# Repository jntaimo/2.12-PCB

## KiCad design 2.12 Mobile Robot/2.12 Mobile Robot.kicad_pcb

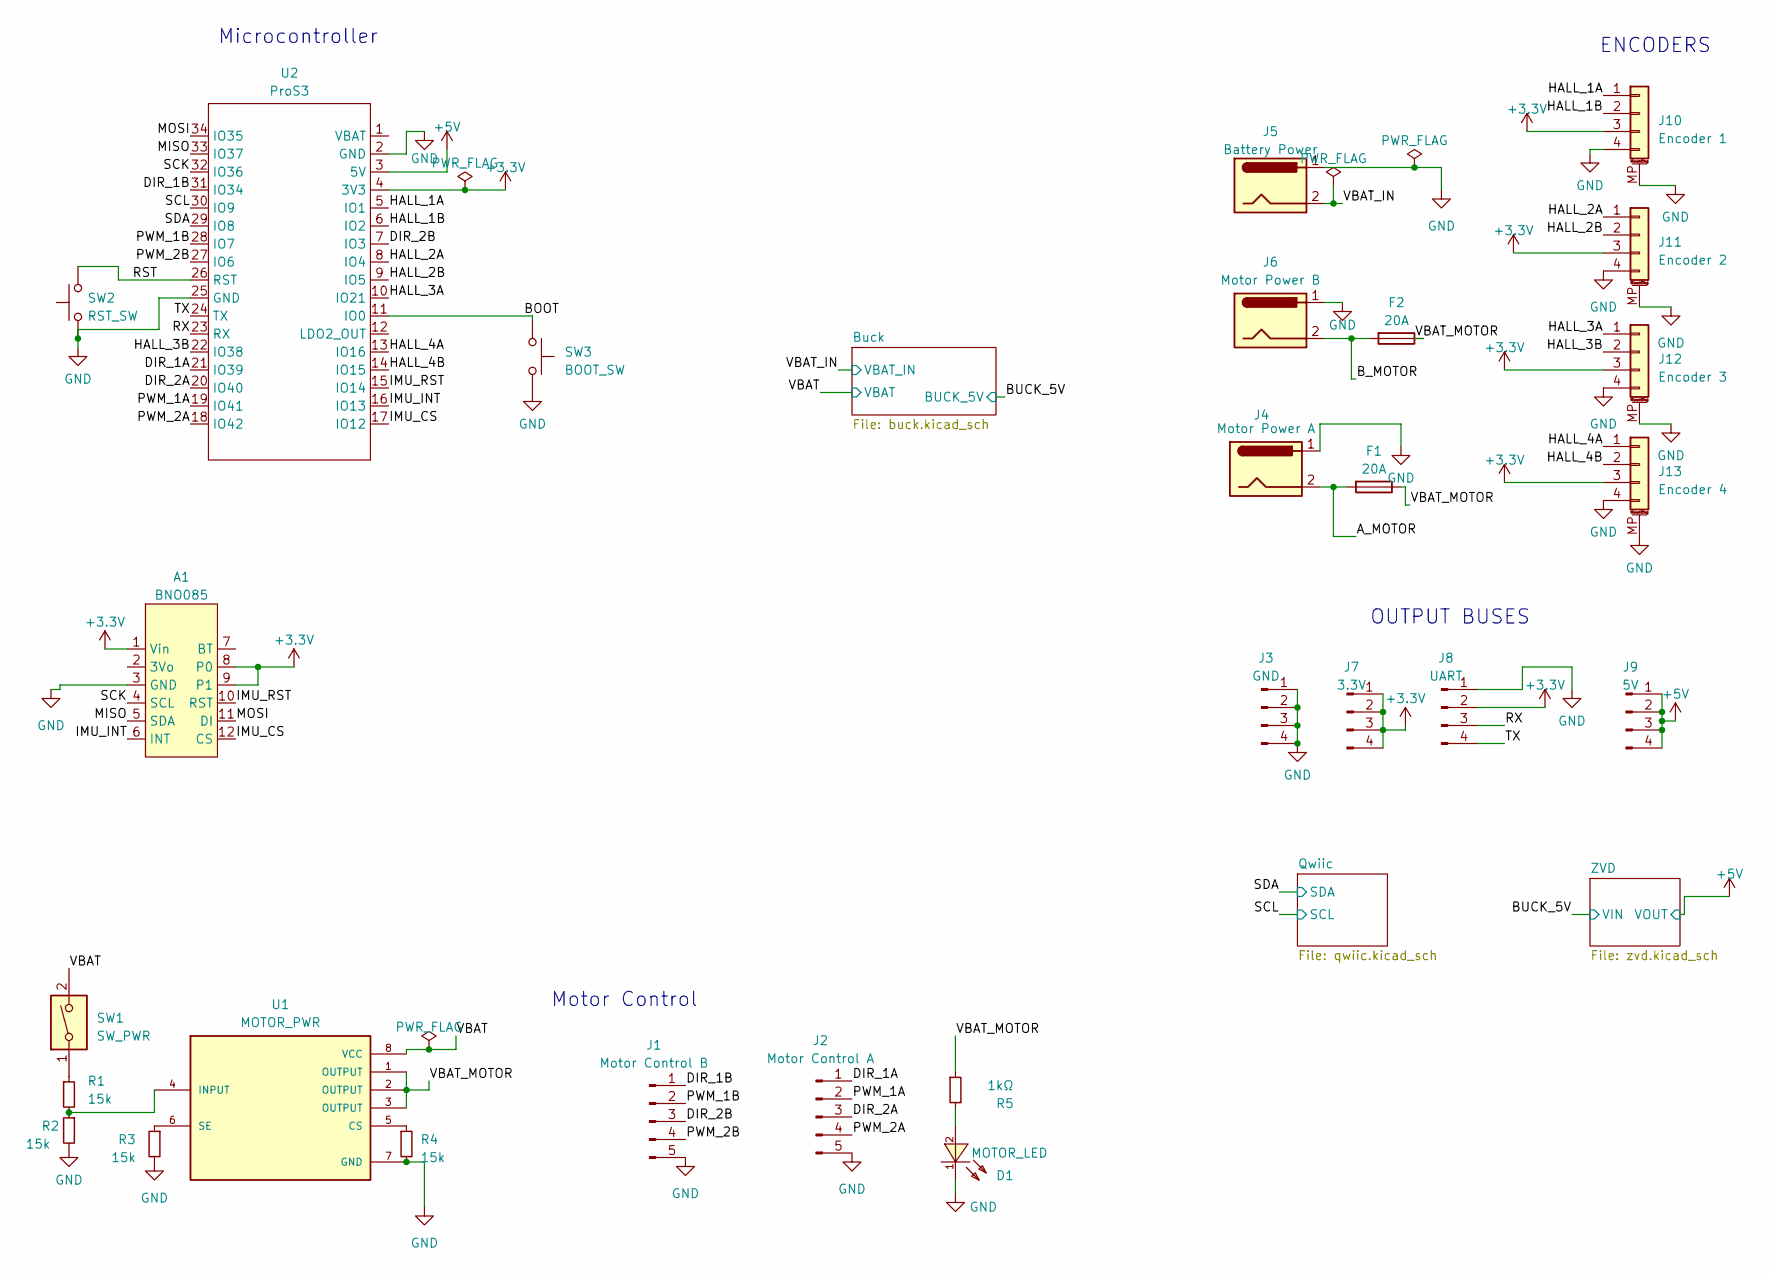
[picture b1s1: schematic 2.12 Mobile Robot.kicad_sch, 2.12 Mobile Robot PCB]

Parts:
A1: BNO085; Adafruit_BNO085
D1: MOTOR_LED; LED0603; LCSC C2286
F1, F2: 20A; Fuse_1206_3216Metric; MPN C207007
J1: Motor Control B; PinHeader_1x05_P2.54mm_Vertical; MPN C492404
J2: Motor Control A; PinHeader_1x05_P2.54mm_Vertical; MPN C492404
J3: GND; PinHeader_1x04_P2.54mm_Vertical; MPN C2691448
J4: Motor Power A; AMASS_XT30PW-F_1x02_P2.50mm_Horizontal; LCSC C2913282
J5: Battery Power; AMASS_XT30PW-M_1x02_P2.50mm_Horizontal; LCSC C2913282
J6: Motor Power B; AMASS_XT30PW-F_1x02_P2.50mm_Horizontal; LCSC C2913282
J7: 3.3V; PinHeader_1x04_P2.54mm_Vertical; MPN C2691448
J8: UART; PinHeader_1x04_P2.54mm_Vertical; MPN C2691448
J9: 5V; PinHeader_1x04_P2.54mm_Vertical; MPN C2691448
J10: Encoder 1; JST_PH_S4B-PH-SM4-TB_1x04-1MP_P2.00mm_Horizontal; MPN C265102
J11: Encoder 2; JST_PH_S4B-PH-SM4-TB_1x04-1MP_P2.00mm_Horizontal; MPN C265102
J12: Encoder 3; JST_PH_S4B-PH-SM4-TB_1x04-1MP_P2.00mm_Horizontal; MPN C265102
J13: Encoder 4; JST_PH_S4B-PH-SM4-TB_1x04-1MP_P2.00mm_Horizontal; MPN C265102
R1, R2, R3, R4: 15k; 0603_1608Metric; MFGPN 0603WAF1502T5E; LCSC C22809
R5: 1kΩ; 0603_1608Metric; MPN C5555492; LCSC C21190
SW1: SW_PWR; JST_PH_B2B-PH-SM4-TB_1x02-1MP_P2.00mm_Vertical; MPN C160352
SW2: RST_SW; SW_PUSH_6mm; MPN C393938
SW3: BOOT_SW; SW_PUSH_6mm; MPN C393938
U1: MOTOR_PWR; DPAK85P972X240-8N; MPN C2150194
U2: ProS3; ProS3_TH

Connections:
+5V: J9.1, J9.2, J9.3, J9.4, U2.3 (5V); also elsewhere on the board
/A_MOTOR: F1.2, J4.2
/BOOT: SW3.1, U2.11 (IO0)
/B_MOTOR: F2.2, J6.2
/DIR_1A: J2.1, U2.21 (IO39)
/DIR_1B: J1.1, U2.31 (IO34)
/DIR_2A: J2.3, U2.20 (IO40)
/DIR_2B: J1.3, U2.7 (IO3)
/HALL_1A: J10.1, U2.5 (IO1)
/HALL_1B: J10.2, U2.6 (IO2)
/HALL_2A: J11.1, U2.8 (IO4)
/HALL_2B: J11.2, U2.9 (IO5)
/HALL_3A: J12.1, U2.10 (IO21)
/HALL_3B: J12.2, U2.22 (IO38)
/HALL_4A: J13.1, U2.13 (IO16)
/HALL_4B: J13.2, U2.14 (IO15)
/IMU_CS: A1.12 (CS), U2.17 (IO12)
/IMU_INT: A1.6 (INT), U2.16 (IO13)
/IMU_RST: A1.10 (RST), U2.15 (IO14)
/MISO: A1.5 (SDA), U2.33 (IO37)
/MOSI: A1.11 (DI), U2.34 (IO35)
/PWM_1A: J2.2, U2.19 (IO41)
/PWM_1B: J1.2, U2.28 (IO7)
/PWM_2A: J2.4, U2.18 (IO42)
/PWM_2B: J1.4, U2.27 (IO6)
/RST: SW2.2, U2.26 (RST)
/RX: J8.3, U2.23 (RX)
/SCK: A1.4 (SCL), U2.32 (IO36)
/SCL: U2.30 (IO9); also elsewhere on the board
/SDA: U2.29 (IO8); also elsewhere on the board
/TX: J8.4, U2.24 (TX)
/VBAT: SW1.2, U1.8 (VCC); also elsewhere on the board
/VBAT_IN: J5.2; also elsewhere on the board
/VBAT_MOTOR: F1.1, F2.1, R5.1, U1.1 (OUTPUT), U1.2 (OUTPUT), U1.3 (OUTPUT)
GND: A1.3 (GND), D1.1 (K), J1.5, J2.5, J3.1, J3.2, J3.3, J3.4, J4.1, J5.1, J6.1, J8.1, J10.4, J10.MP (MountPin), J11.4, J11.MP (MountPin), J12.4, J12.MP (MountPin), J13.4, J13.MP (MountPin), R2.2, R3.2, R4.2, SW2.1, SW3.2, U1.7 (GND), U2.2 (GND), U2.25 (GND); also elsewhere on the board
unnamed: D1.2 (A), R5.2
unnamed: R1.1, SW1.1
unnamed: R4.1, U1.5 (CS)
unnamed: R1.2, R2.1, U1.4 (INPUT)
unnamed: R3.1, U1.6 (SE)

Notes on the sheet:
OUTPUT BUSES
ENCODERS
Microcontroller
Motor Control

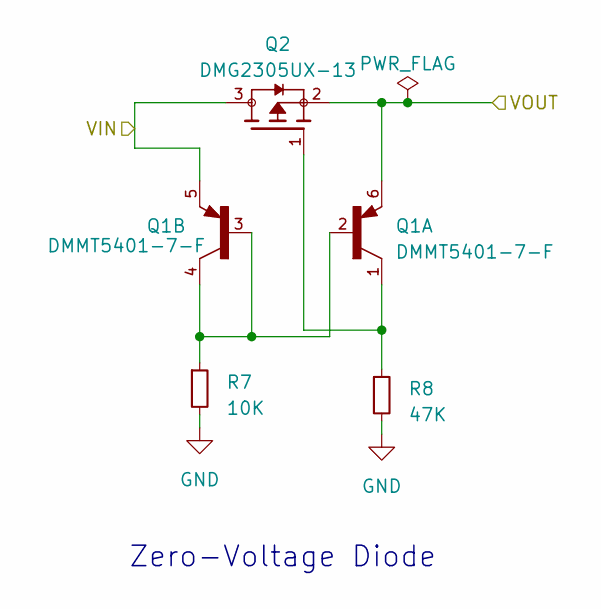
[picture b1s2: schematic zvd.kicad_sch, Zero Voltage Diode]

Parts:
Q1: DMMT5401-7-F; SOT95P285X140-6N; PARTREV 8
Q2: DMG2305UX-13; SOT91P240X110-3N; PARTREV 09/2018
R7: 10K; 0603_1608Metric; MPN C22548; LCSC C25804
R8: 47K; 0603_1608Metric; MPN C25792; LCSC C25819

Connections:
+5V: Q1.6, Q2.2; also elsewhere on the board
/BUCK_5V: Q1.5, Q2.3; also elsewhere on the board

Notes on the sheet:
Zero-Voltage Diode

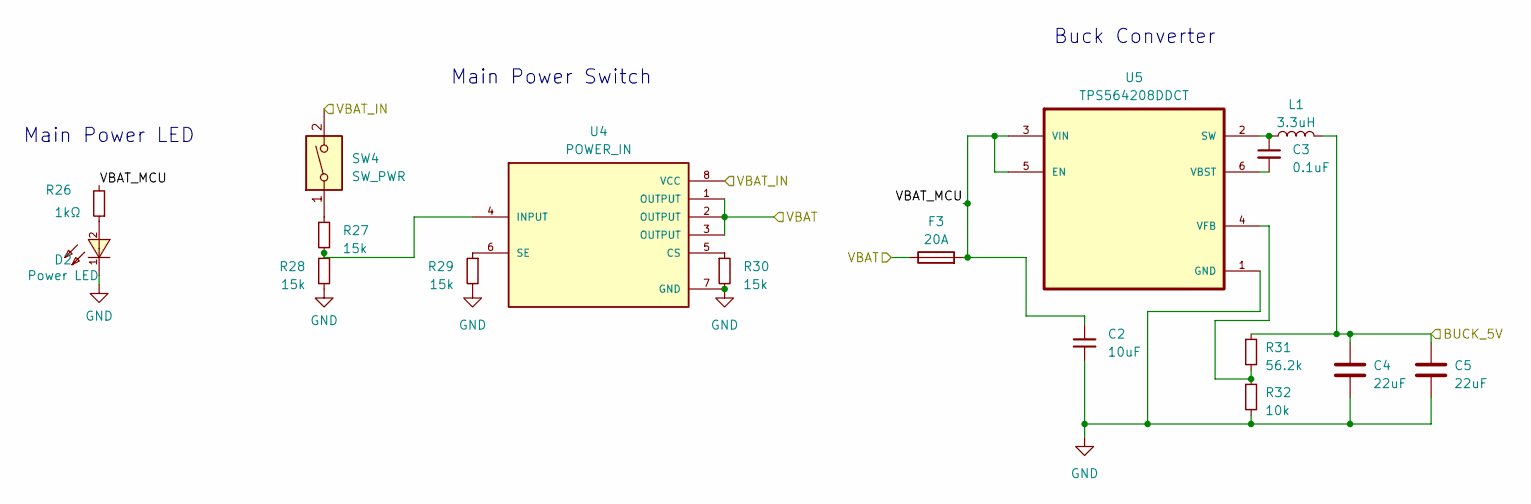
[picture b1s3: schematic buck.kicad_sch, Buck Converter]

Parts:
C2: 10uF; 0805_2012Metric; MPN C39232; LCSC C15850
C3: 0.1uF; C_0805_2012Metric; MPN C519981
C4, C5: 22uF; C_1210_3225Metric; MPN C65428
D2: Power LED; LED0603; MPN C84263; LCSC C72043
F3: 20A; Fuse_1206_3216Metric; MPN C207007
L1: 3.3uH; L_Vishay_IHLP-4040; MPN C845075
R26: 1kΩ; 0603_1608Metric; MPN C5555492; LCSC C21190
R27, R28, R29, R30: 15k; 0603_1608Metric; MFGPN 0603WAF1502T5E; LCSC C22809
R31: 56.2k; 0603_1608Metric; MFGPN RC0603FR-0756K2L; LCSC C482887
R32: 10k; 0603_1608Metric; MPN C22548; LCSC C25804
SW4: SW_PWR; JST_PH_B2B-PH-SM4-TB_1x02-1MP_P2.00mm_Vertical; MPN C160352
U4: POWER_IN; DPAK85P972X240-8N; MPN C2150194
U5: TPS564208DDCT; SOT95P280X110-6N; MPN C2070774

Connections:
/BUCK_5V: C4.1, C5.1, L1.2, R31.1; also elsewhere on the board
/Buck/VBAT_MCU: C2.1, F3.2, R26.2, U5.3 (VIN), U5.5 (EN)
/VBAT: F3.1, U4.1 (OUTPUT), U4.2 (OUTPUT), U4.3 (OUTPUT); also elsewhere on the board
/VBAT_IN: SW4.2, U4.8 (VCC); also elsewhere on the board
GND: C2.2, C4.2, C5.2, D2.1 (C), R28.2, R29.2, R30.2, R32.2, U4.7 (GND), U5.1 (GND); also elsewhere on the board
unnamed: D2.2 (A), R26.1
unnamed: R27.1, SW4.1
unnamed: R30.1, U4.5 (CS)
unnamed: R27.2, R28.1, U4.4 (INPUT)
unnamed: R29.1, U4.6 (SE)
unnamed: C3.1, L1.1, U5.2 (SW)
unnamed: C3.2, U5.6 (VBST)
unnamed: R31.2, R32.1, U5.4 (VFB)

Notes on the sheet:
Main Power Switch
Main Power LED
Buck Converter

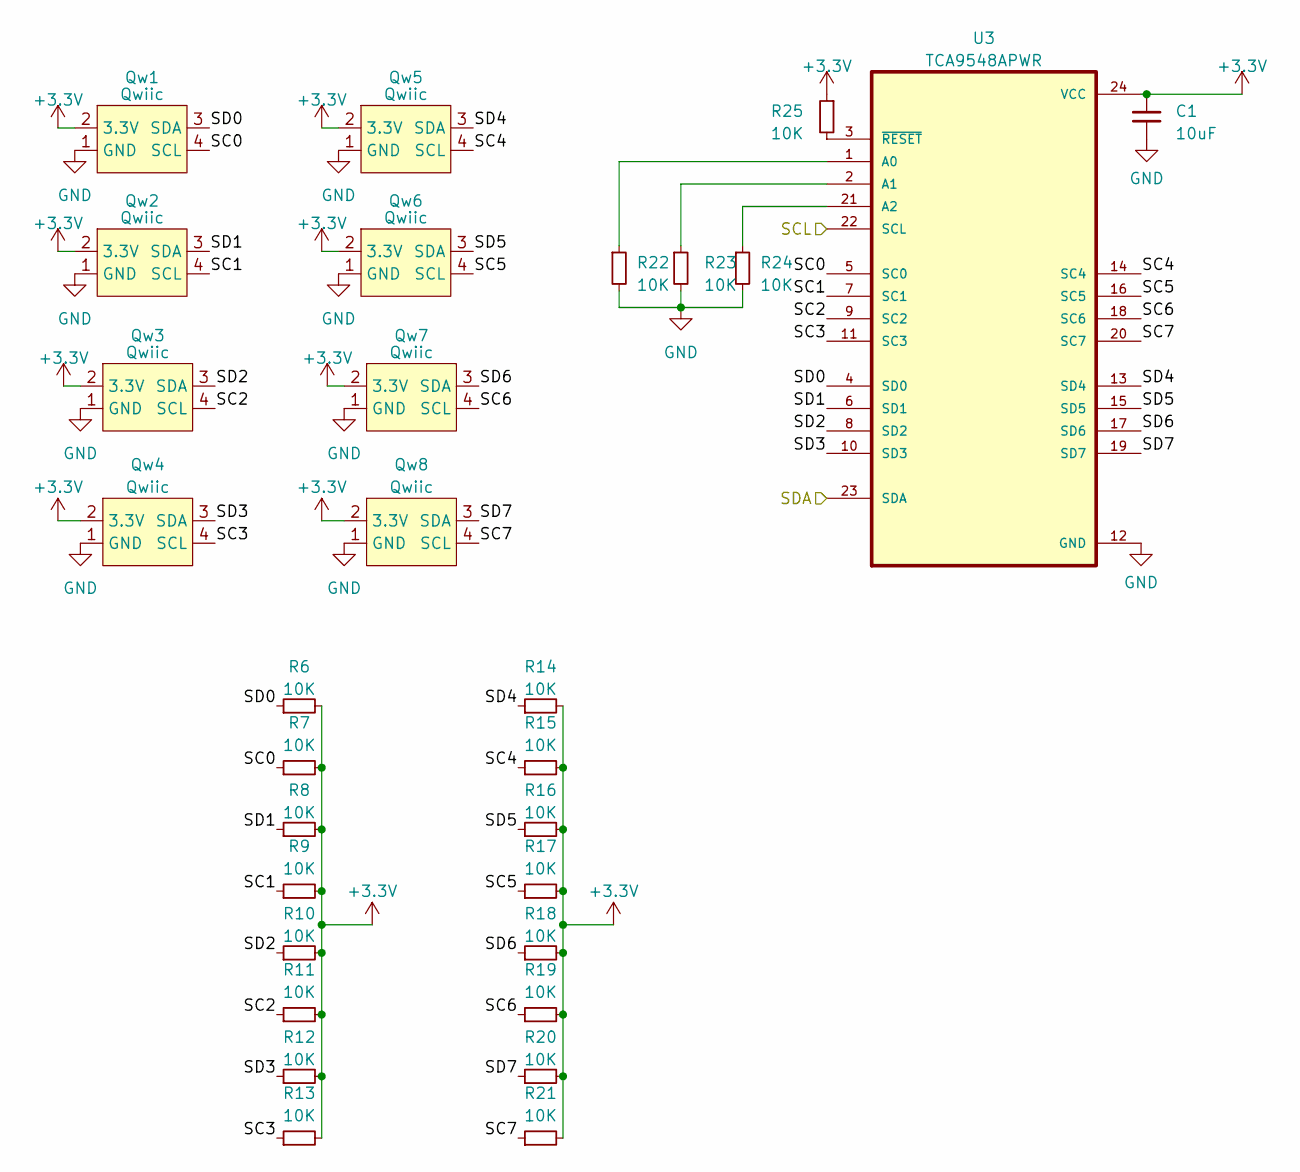
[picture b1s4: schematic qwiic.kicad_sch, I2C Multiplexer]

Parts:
C1: 10uF; 0805_2012Metric; MPN C39232; LCSC C15850
Qw1, Qw2, Qw3, Qw4, Qw5, Qw6, Qw7, Qw8: Qwiic; JST_SH_BM04B-SRSS-TB_1x04-1MP_P1.00mm_Vertical; MPN C160390
R6, R7, R8, R9, R10, R11, R12, R13, R14, R15, R16, R17, R18, R19, R20, R21, R22, R23, R24, R25: 10K; 0603_1608Metric; MPN C22548; LCSC C25804
U3: TCA9548APWR; SOP65P640X120-24N; MPN C130026

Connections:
/Qwiic/SC1: Qw2.4 (SCL), R9.1, U3.7 (SC1)
/Qwiic/SC2: Qw3.4 (SCL), R11.1, U3.9 (SC2)
/Qwiic/SC3: Qw4.4 (SCL), R13.1, U3.11 (SC3)
/Qwiic/SC4: Qw5.4 (SCL), R15.1, U3.14 (SC4)
/Qwiic/SC5: Qw6.4 (SCL), R17.1, U3.16 (SC5)
/Qwiic/SC6: Qw7.4 (SCL), R19.1, U3.18 (SC6)
/Qwiic/SC7: Qw8.4 (SCL), R21.1, U3.20 (SC7)
/Qwiic/SD0: Qw1.3 (SDA), R6.1, U3.4 (SD0)
/Qwiic/SD2: Qw3.3 (SDA), R10.1, U3.8 (SD2)
/Qwiic/SD3: Qw4.3 (SDA), R12.1, U3.10 (SD3)
/Qwiic/SD4: Qw5.3 (SDA), R14.1, U3.13 (SD4)
/Qwiic/SD5: Qw6.3 (SDA), R16.1, U3.15 (SD5)
/Qwiic/SD6: Qw7.3 (SDA), R18.1, U3.17 (SD6)
/Qwiic/SD7: Qw8.3 (SDA), R20.1, U3.19 (SD7)
/SCL: U3.22 (SCL); also elsewhere on the board
/SDA: U3.23 (SDA); also elsewhere on the board
GND: C1.2, Qw1.1 (GND), Qw2.1 (GND), Qw3.1 (GND), Qw4.1 (GND), Qw5.1 (GND), Qw6.1 (GND), Qw7.1 (GND), Qw8.1 (GND), R22.2, R23.2, R24.2, U3.12 (GND); also elsewhere on the board
unnamed: R22.1, U3.1 (A0)
unnamed: R23.1, U3.2 (A1)
unnamed: R24.1, U3.21 (A2)
unnamed: R25.2, U3.3 (~RESET)

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
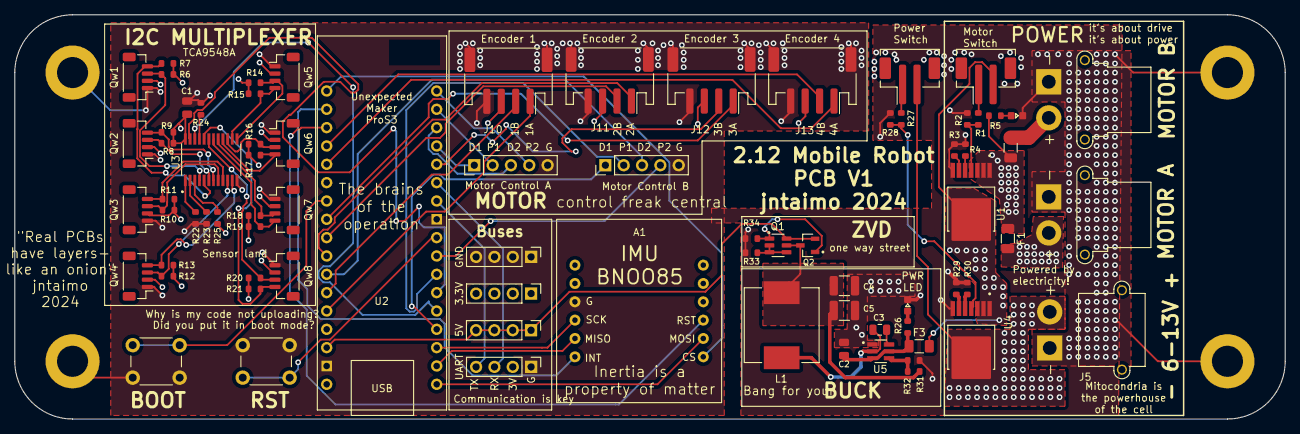
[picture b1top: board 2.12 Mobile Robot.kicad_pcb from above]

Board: 4 copper layers, 176.0 x 56.0 mm, 78 parts (0 on the bottom side), 73 nets.

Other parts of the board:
R33: 10K; 0603_1608Metric
R34: 47K; 0603_1608Metric

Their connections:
GND: R33.2, R34.2; also elsewhere on the board

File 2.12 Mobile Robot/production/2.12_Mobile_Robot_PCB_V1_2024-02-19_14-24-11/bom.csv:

Designator,Footprint,Quantity,Value,LCSC Part #
"C1, C2",0805_2012Metric,2,10uF,C15850
C3,0805,1,0.1uF,C519981
"C4, C5",1210,2,22uF,C65428
D1,LED0603,1,MOTOR_LED,C2286
D2,LED0603,1,Power LED,C72043
"F1, F2, F3",1206,3,20A,C207007
J1,PinHeader_1x05_P2.54mm_Vertical,1,Motor Control R,C492404
J10,JST_PH_S4B-PH-SM4-TB_1x04-1MP_P2.00mm_Horizontal,1,FL Encoder,C265102
J11,JST_PH_S4B-PH-SM4-TB_1x04-1MP_P2.00mm_Horizontal,1,BL Encoder,C265102
J12,JST_PH_S4B-PH-SM4-TB_1x04-1MP_P2.00mm_Horizontal,1,FR Encoder,C265102
J13,JST_PH_S4B-PH-SM4-TB_1x04-1MP_P2.00mm_Horizontal,1,BR Encoder,C265102
J2,PinHeader_1x05_P2.54mm_Vertical,1,Motor Control L,C492404
J3,PinHeader_1x04_P2.54mm_Vertical,1,GND,C2691448
J4,AMASS_XT30PW-F_1x02_P2.50mm_Horizontal,1,Motor Power R,C2913282
J5,AMASS_XT30PW-M_1x02_P2.50mm_Horizontal,1,Battery Power,C2913282
J6,AMASS_XT30PW-F_1x02_P2.50mm_Horizontal,1,Motor Power L,C2913282
J7,PinHeader_1x04_P2.54mm_Vertical,1,3.3V,C2691448
J8,PinHeader_1x04_P2.54mm_Vertical,1,UART,C2691448
J9,PinHeader_1x04_P2.54mm_Vertical,1,5V,C2691448
L1,L_Vishay_IHLP-4040,1,3.3uH,C845075
Q1,SOT95P285X140-6N,1,DMMT5401-7-F,C154733
Q2,SOT91P240X110-3N,1,DMG2305UX-13,C144153
"Qw1, Qw2, Qw3, Qw4, Qw5, Qw6, Qw7, Qw8",JST_SH_BM04B-SRSS-TB_1x04-1MP_P1.00mm_Vertical,8,Qwiic,C160390
"R1, R2, R27, R28, R29, R3, R30, R4",0603_1608Metric,8,15k,C22809
"R10, R11, R12, R13, R14, R15, R16, R17, R18, R19, R20, R21, R22, R23, R24, R25, R32, R33, R6, R7, R8, R9",0603_1608Metric,22,10K,C25804
"R26, R5",0603_1608Metric,2,1kΩ,C21190
R31,0603_1608Metric,1,56.2k,C482887
R34,0603_1608Metric,1,47K,C25819
"SW1, SW4",JST_PH_B2B-PH-SM4-TB_1x02-1MP_P2.00mm_Vertical,2,SW_PWR,C160352
SW2,SW_PUSH_6mm,1,RST_SW,C393938
SW3,SW_PUSH_6mm,1,BOOT_SW,C393938
U1,DPAK85P972X240-8N,1,MOTOR_PWR,C2150194
U3,SOP65P640X120-24N,1,TCA9548APWR,C130026
U4,DPAK85P972X240-8N,1,POWER_IN,C2150194
U5,SOT95P280X110-6N,1,TPS564208DDCT,C2070774

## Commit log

2024-01-26 Intial commit
2024-01-30 Added hierarchical sheets
2024-01-30 Passed DRC
2024-02-03 Changed some of the footprints
2024-02-12 Renamed stuff
2024-02-16 Fully routed
2024-02-16 Made footprints from project libraries
2024-02-16 Finesse
2024-02-17 Added silkscreen callouts and fixed resistors
2024-02-17 Fixed thermal reliefs on pour
2024-02-18 About to add JLCPCB libraries
2024-02-19 Tentatively ready for production
2024-02-19 Added JLCPCB Library
2024-02-20 Production files
2024-02-24 Updated silkscreen to be generic
2024-02-24 fixed silkscreen error
2024-03-19 bonus
2024-08-05 Backing up
2024-08-05 Updated to Kicad 8
